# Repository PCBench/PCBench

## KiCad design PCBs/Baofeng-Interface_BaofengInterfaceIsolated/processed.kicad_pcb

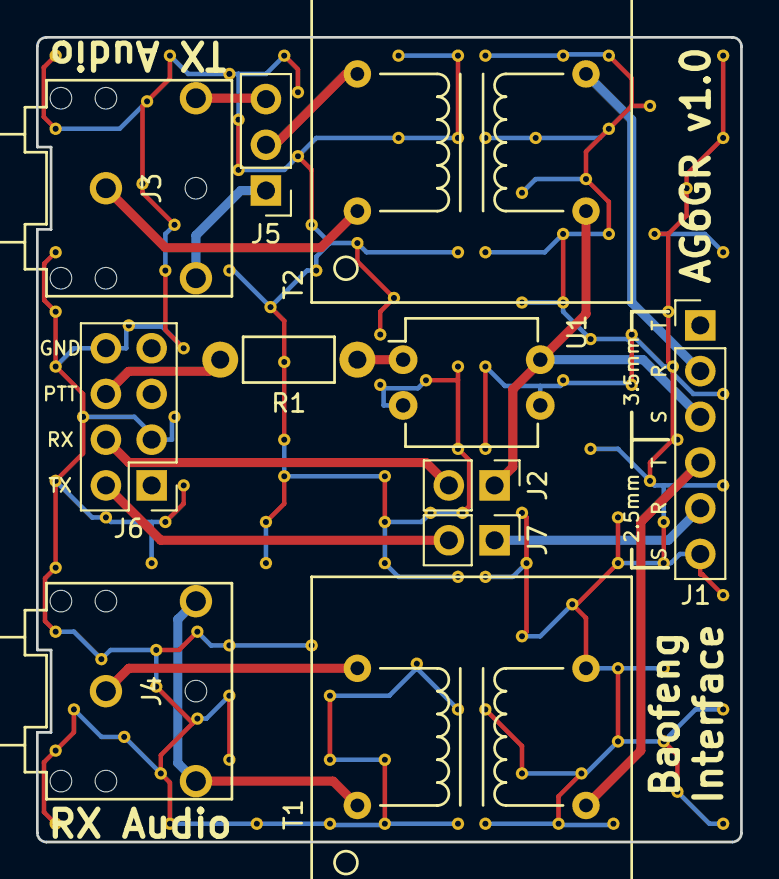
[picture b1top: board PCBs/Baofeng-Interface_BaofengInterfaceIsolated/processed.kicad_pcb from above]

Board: 2 copper layers, 39.1 x 44.7 mm, 11 parts (0 on the bottom side), 16 nets.

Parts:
J1: CONN_01X06; Pin_Header_Straight_1x06_Pitch2.54mm
J2, J7: CONN_01X02; Pin_Header_Straight_1x02_Pitch2.54mm
J3, J4: JACK_TRS_3PINS; SJ1-352XN
J5: CONN_01X03; Pin_Header_Straight_1x03_Pitch2.54mm
J6: CONN_02X04; Pin_Header_Straight_2x04_Pitch2.54mm
R1: 100; Resistor_Horizontal_RM7mm
T1, T2: LM-NP-1001-B1L; LM-LP-1001L
U1: LTV-817; DIP-4_W7.62mm

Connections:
GND: J6.3, J6.8, U1.2
GNDA: J1.6, T1.5, U1.3
unnamed: J1.5, J7.1
unnamed: J3.1, T2.1
unnamed: J4.1, T1.4
unnamed: J4.2, J4.3, T1.1
unnamed: J5.2, T2.4
unnamed: R1.1, U1.1
PTT_B: J6.6, R1.2
RX_AUDIO: J1.4, T1.8
SERIAL_RX: J2.2, J6.4
SERIAL_TX: J6.2, J7.2
TX_AUDIO+: J1.2, T2.5
TX_AUDIO-: J1.3, J2.1, T2.8, U1.4
TX_LEFT+: J3.3, J5.3
TX_RIGHT+: J3.2, J5.1

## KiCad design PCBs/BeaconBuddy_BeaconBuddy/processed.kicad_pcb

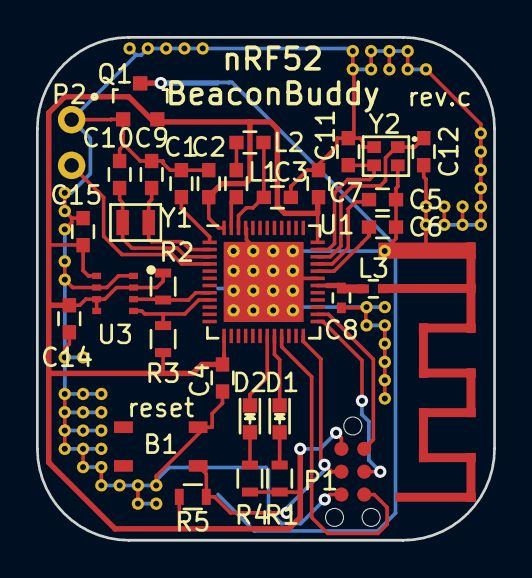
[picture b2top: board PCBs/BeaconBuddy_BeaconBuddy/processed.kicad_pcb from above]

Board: 2 copper layers, 25.4 x 27.9 mm, 34 parts (1 on the bottom side), 26 nets.

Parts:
A1: Antenna; Antenna-2.45GHZ
B1: SKRPABE010
BT1: BAT-HLD-001; BATT-HLD-001
C1, C4, C7, C14, C15: 0.1uF; C_0603
C2: 4.7uF; C_0603
C3: 1uF; C_0603
C5: 100pF; C_0603
C6: NC; C_0603
C8: 0.8pF; C_0402
C9, C10, C11, C12: 12pF; C_0603
D1: L0603G; LED_0603
D2: L0603R; LED_0603
L1: 10uH; C_0603
L2: 15nH; C_0603
L3: 3.9nH; C_0402
P1: CONN_01X06; TC2030-MCP-NL
P2: AIN0; CONN_100mil_1x2
Q1: Si2365EDS; SOT-23
R1, R4: 470; R_0603
R2, R3: 4.7k; R_0603
R5: 10k; R_0603
U1: nRF52832-QFAA; UQFN-48-1EP_6x6mm_Pitch0.4mm
U3: BME280; Bosch_LGA8_2.5x2.5
Y1: 32.768kHz; Crystal_ABS06
Y2: 32MHz; Crystal_ABM11

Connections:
/AIN0: P2.2, U1.4
/ANT: C8.1, L3.2, U1.30
/RF_OUT: A1.1, L3.1
/SCL: R3.2, U1.9, U3.4
/SDA: R2.2, U1.8, U3.3
/SWDCLK: P1.4, U1.25
/SWDIO: P1.2, U1.26
/SWO: P1.6, U1.21
/XC1: C11.2, U1.35, Y2.3
/XC2: C12.2, U1.34, Y2.1
/XL1: C9.2, U1.2, Y1.1
/XL2: C10.2, U1.3, Y1.2
/nRESET: B1.1, P1.3, R5.2, U1.24
GND: A1.2, B1.3, BT1.2, C1.2, C2.2, C3.2, C4.2, C5.1, C6.1, C7.2, C8.2, C9.1, C10.1, C11.1, C12.1, C14.2, C15.2, P1.5, P2.1, Q1.1, U1.31, U1.45, U1.49, U3.1, U3.7, Y2.2, Y2.4
unnamed: BT1.1, Q1.3
unnamed: C1.1, U1.1
unnamed: C3.1, L2.1, U1.46
unnamed: C5.2, U1.33
unnamed: C6.2, U1.32
unnamed: D1.1, U1.20
unnamed: D1.2, R1.1
unnamed: D2.1, U1.19
unnamed: D2.2, R4.1
unnamed: L1.1, L2.2
unnamed: L1.2, U1.47
VDD: C2.1, C4.1, C7.1, C14.1, C15.1, P1.1, Q1.2, R1.2, R2.1, R3.1, R4.2, R5.1, U1.13, U1.36, U1.48, U3.2, U3.5, U3.6, U3.8

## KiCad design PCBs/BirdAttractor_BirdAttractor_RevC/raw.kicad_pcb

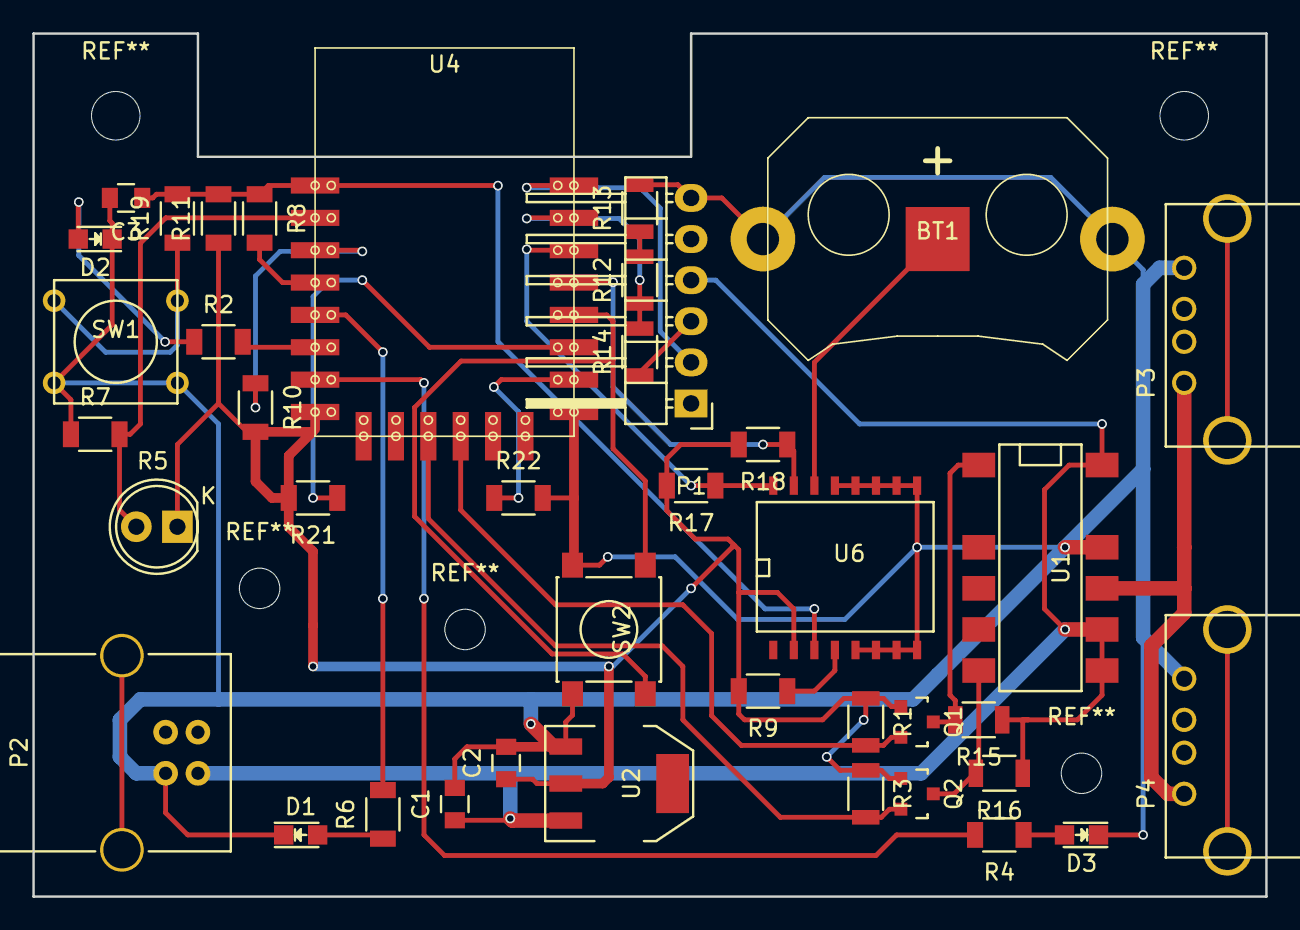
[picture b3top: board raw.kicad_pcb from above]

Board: 2 copper layers, 76.2 x 53.3 mm, 40 parts (0 on the bottom side), 30 nets.

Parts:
BT1: 3V Battery; BK-913
C1, C2: 10uF; C_0805
C3: 0.1uF; C_0805
D1, D2, D3: LED; LED-0805
P1: FTDI; Pin_Header_Angled_1x06
P2: USB_B
P3, P4: USB_A
Q1, Q2: BSS138; SOT-23
R1, R3, R12, R13, R15, R16: 10K; R_1206
R2, R4: 68; C_1206
R5: Photores; LED-5MM
R6: 18; C_1206
R7, R19: 1K; C_1206
R8: 2.7K; C_1206
R9, R10, R11, R21, R22: 10K; C_1206
R14: 10K/0; R_1206
R17, R18: 47K; C_1206
SW1: SW_PUSH; SW_PUSH_SMALL
SW2: SW_PUSH; SW_SPST_PTS645
U1: PR_Relay_V23079; DIP-12-SMD
U2: AMS1117-3.3; SOT-223
U4: ESP8266-12E; ESP8266-12E-80
U6: DS3231; SO-16-W

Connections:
5V_IN: C1.1, P1.4, P2.1, R15.1, R16.1, U1.7, U1.8, U1.12, U2.3
5V_OUT: P3.1, P4.1, U1.9
ADC: R5.2, R7.2, U4.2
ALARM_WAKE: C3.1, R8.1, R11.2, R19.2, U4.1, U6.3
CH_PD: R10.1, U4.3
DEEP_SLEEP_WAKE: R8.2, U4.4
GND: BT1.2, C1.2, C2.2, C3.2, D1.1, D2.1, D3.1, P1.6, P2.4, P3.4, P4.4, R7.1, R13.2, R22.2, SW1.2, SW2.2, U1.10, U2.1, U4.15, U6.5, U6.6, U6.7, U6.8, U6.9, U6.10, U6.11, U6.12, U6.13
LED_5V_IN: R2.2, U4.6
LED_5V_OUT: R4.2, U4.7
LED_WIFI: R6.2, U4.5
unnamed: D1.2, R6.1
unnamed: D2.2, R2.1
unnamed: D3.2, R4.1
unnamed: R9.1, U6.4
unnamed: R12.2, R13.1
unnamed: R19.1, SW1.1
unnamed: R21.1, U4.17
unnamed: R22.1, U4.16
PROGRAM: SW2.1, U4.18
RELAY_OFF: Q1.3, R15.2, U1.1
RELAY_OFF33: Q1.2, R1.2, U4.12
RELAY_ON: Q2.3, R16.2, U1.6
RELAY_ON33: Q2.2, R3.2, U4.11
RX: P1.3, R14.1
RX33: R12.1, R14.2, U4.21
SCL: R17.1, U4.20, U6.16
SDA: R18.1, U4.19, U6.15
TX: P1.2, U4.22
V33: C2.1, Q1.1, Q2.1, R1.1, R3.1, R5.1, R9.2, R10.2, R11.1, R17.2, R18.2, R21.2, U2.2, U4.8, U6.2
VBAT: BT1.1, U6.14

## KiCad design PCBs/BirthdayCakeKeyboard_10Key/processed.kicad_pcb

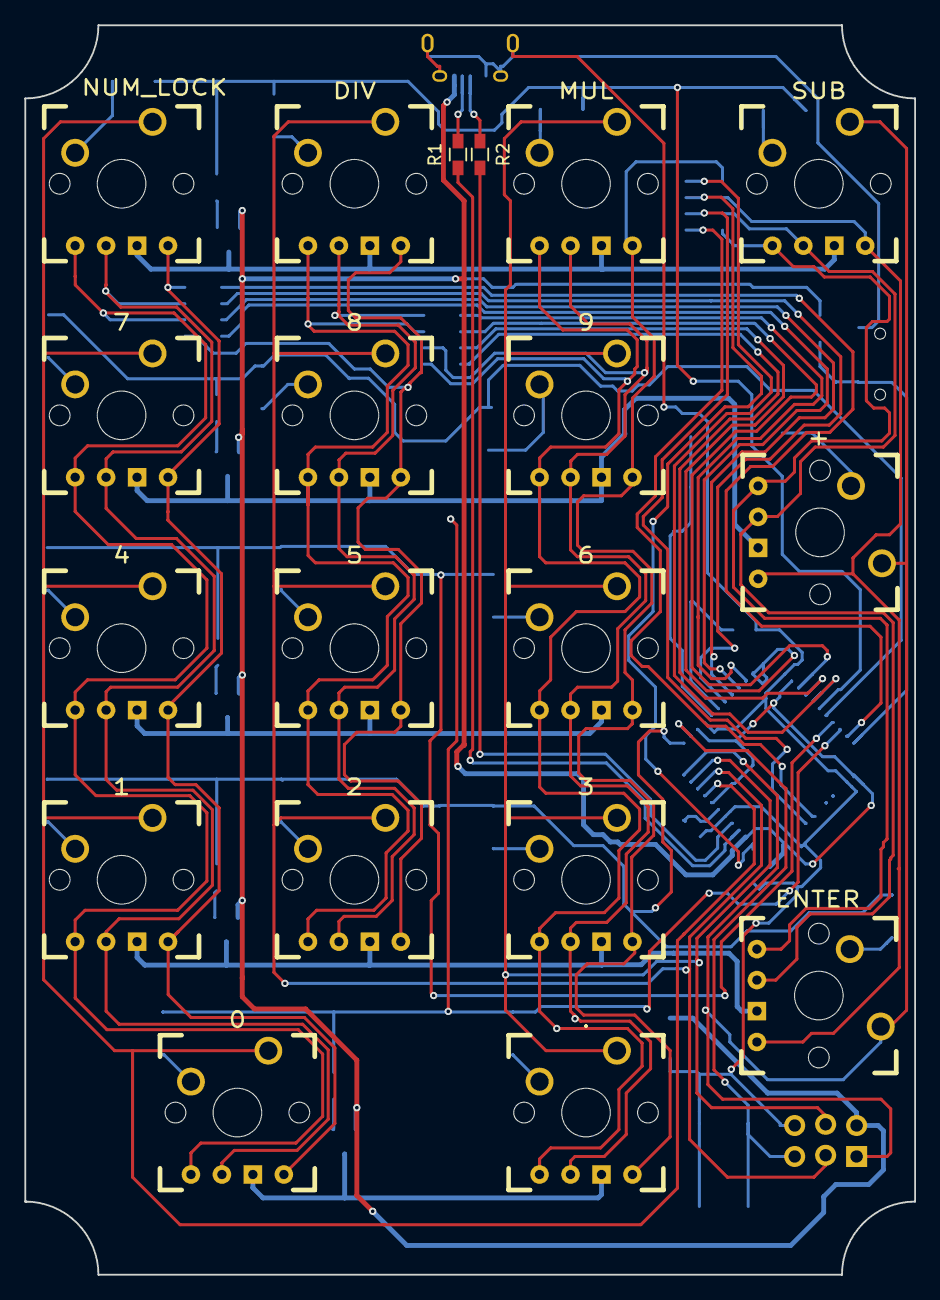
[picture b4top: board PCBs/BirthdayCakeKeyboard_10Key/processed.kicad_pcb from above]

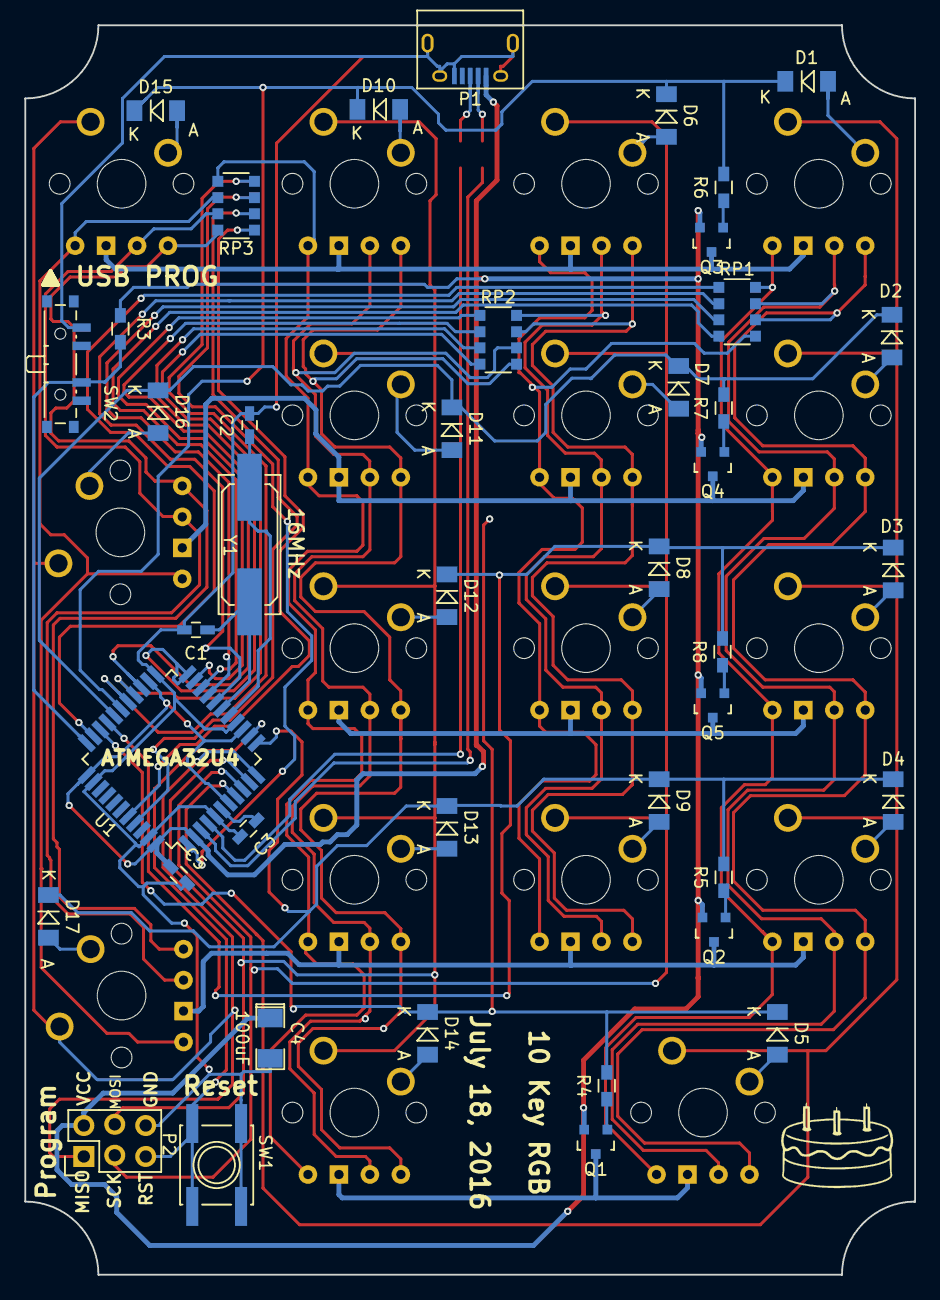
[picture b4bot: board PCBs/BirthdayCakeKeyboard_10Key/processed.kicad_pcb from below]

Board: 2 copper layers, 73.0 x 102.5 mm, 65 parts (46 on the bottom side), 71 nets.

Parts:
C1, C2: 18pF; C_0603_HandSoldering
C3: .1uF; C_0603_HandSoldering
C4: 100uF; SMD-1206_Pol
C5: 0.1uF; C_0603_HandSoldering
D1, D2, D3, D4, D5, D6, D7, D8, D9, D10, D11, D12, D13, D14, D15, D16, D17: D; MiniMELF_Standard
Noname_1: BirthdayCake
Noname_2, Noname_3, Noname_4: Flame
P1: USB_OTG; USB_Micro-B
P2: Program; Pin_Header_Straight_2x03
Q1, Q2, Q3, Q4, Q5: MMBT3906; SOT-23
R1, R2: 22; R_0603_HandSoldering
R3: 10k; R_0603_HandSoldering
R4, R5, R6, R7, R8: 1K; R_0603_HandSoldering
RP1, RP2, RP3: 100; R_Array_Convex_4x1206
SW1: SW_PUSH; SW_SPST_EVQQ2
SW2: USB PROG; SW_SP3T_PCM13
SW3: NUM_LOCK; Zealios_Cherry_MX
SW4: 7; Zealios_Cherry_MX
SW5: 4; Zealios_Cherry_MX
SW6: 1; Zealios_Cherry_MX
SW7: 0; Zealios_Cherry_MX
SW8: DIV; Zealios_Cherry_MX
SW9: 8; Zealios_Cherry_MX
SW10: 5; Zealios_Cherry_MX
SW11: 2; Zealios_Cherry_MX
SW12: MUL; Zealios_Cherry_MX
SW13: 9; Zealios_Cherry_MX
SW14: 6; Zealios_Cherry_MX
SW15: 3; Zealios_Cherry_MX
SW16: .; Zealios_Cherry_MX
SW17: SUB; Zealios_Cherry_MX
SW18: +; Zealios_Cherry_MX
SW19: ENTER; Zealios_Cherry_MX
U1: ATMEGA32U4-A; LQFP-44_10x10mm_Pitch0.8mm
Y1: 16Mhz; Q_49U3HMS

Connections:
/COL0: SW3.1, SW4.1, SW5.1, SW6.1, SW7.1, U1.8
/COL1: P2.3, SW8.1, SW9.1, SW10.1, SW11.1, U1.9
/COL2: P2.4, SW12.1, SW13.1, SW14.1, SW15.1, SW16.1, U1.10
/COL3: P2.1, SW17.1, SW18.1, SW19.1, U1.11
/LEDB0: RP1.6, SW3.6, SW4.6, SW5.6, SW6.6, SW7.6
/LEDB1: RP2.7, SW8.6, SW9.6, SW10.6, SW11.6
/LEDB2: RP2.5, SW12.6, SW13.6, SW14.6, SW15.6, SW16.6
/LEDB3: RP3.8, SW17.6, SW18.6, SW19.6
/LEDG0: RP1.7, SW3.5, SW4.5, SW5.5, SW6.5, SW7.5
/LEDG1: RP2.8, SW8.5, SW9.5, SW10.5, SW11.5
/LEDG2: RP2.6, SW12.5, SW13.5, SW14.5, SW15.5, SW16.5
/LEDG3: RP3.7, SW17.5, SW18.5, SW19.5
/LEDR0: RP1.8, SW3.3, SW4.3, SW5.3, SW6.3, SW7.3
/LEDR1: RP1.5, SW8.3, SW9.3, SW10.3, SW11.3
/LEDR2: RP3.5, SW12.3, SW13.3, SW14.3, SW15.3, SW16.3
/LEDR3: RP3.6, SW17.3, SW18.3, SW19.3
/PROGRAM: R3.2, SW2.2, U1.33
/ROW0: D1.1, D6.1, D10.1, D15.1, R6.2, U1.28
/ROW1: D2.1, D7.1, D11.1, D16.1, R7.2, U1.29
/ROW2: D3.1, D8.1, D12.1, R8.2, U1.30
/ROW3: D4.1, D9.1, D13.1, D17.1, R5.2, U1.12
/ROW4: D5.1, D14.1, R4.2, U1.31
/RST: P2.5, SW1.2, U1.13
/USBDMinus: R1.1, U1.3
/USBDPlus: R2.1, U1.4
GND: C1.2, C2.2, C3.2, C4.2, C5.2, P1.5, P1.6, P2.6, SW1.1, SW2.1, U1.5, U1.15, U1.23, U1.35, U1.43
unnamed: C1.1, U1.17, Y1.1
unnamed: C2.1, U1.16, Y1.2
unnamed: C3.1, U1.6
unnamed: D1.2, SW3.2
unnamed: D2.2, SW4.2
unnamed: D3.2, SW5.2
unnamed: D4.2, SW6.2
unnamed: D5.2, SW7.2
unnamed: D6.2, SW8.2
unnamed: D7.2, SW9.2
unnamed: D8.2, SW10.2
unnamed: D9.2, SW11.2
unnamed: D10.2, SW12.2
unnamed: D11.2, SW13.2
unnamed: D12.2, SW14.2
unnamed: D13.2, SW15.2
unnamed: D14.2, SW16.2
unnamed: D15.2, SW17.2
unnamed: D16.2, SW18.2
unnamed: D17.2, SW19.2
unnamed: P1.2, R1.2
unnamed: P1.3, R2.2
unnamed: Q1.1, R4.1
unnamed: Q1.3, SW7.4, SW16.4
unnamed: Q2.1, R5.1
unnamed: Q2.3, SW6.4, SW11.4, SW15.4, SW19.4
unnamed: Q3.1, R6.1
unnamed: Q3.3, SW3.4, SW8.4, SW12.4, SW17.4
unnamed: Q4.1, R7.1
unnamed: Q4.3, SW4.4, SW9.4, SW13.4, SW18.4
unnamed: Q5.1, R8.1
unnamed: Q5.3, SW5.4, SW10.4, SW14.4
unnamed: RP1.1, U1.32
unnamed: RP1.2, U1.18
unnamed: RP1.3, U1.19
unnamed: RP1.4, U1.20
unnamed: RP2.1, U1.21
unnamed: RP2.2, U1.25
unnamed: RP2.3, U1.22
unnamed: RP2.4, U1.26
unnamed: RP3.1, U1.40
unnamed: RP3.2, U1.41
unnamed: RP3.3, U1.1
unnamed: RP3.4, U1.27
VCC: C4.1, C5.1, P1.1, P2.2, Q1.2, Q2.2, Q3.2, Q4.2, Q5.2, R3.1, U1.2, U1.7, U1.14, U1.24, U1.34, U1.44

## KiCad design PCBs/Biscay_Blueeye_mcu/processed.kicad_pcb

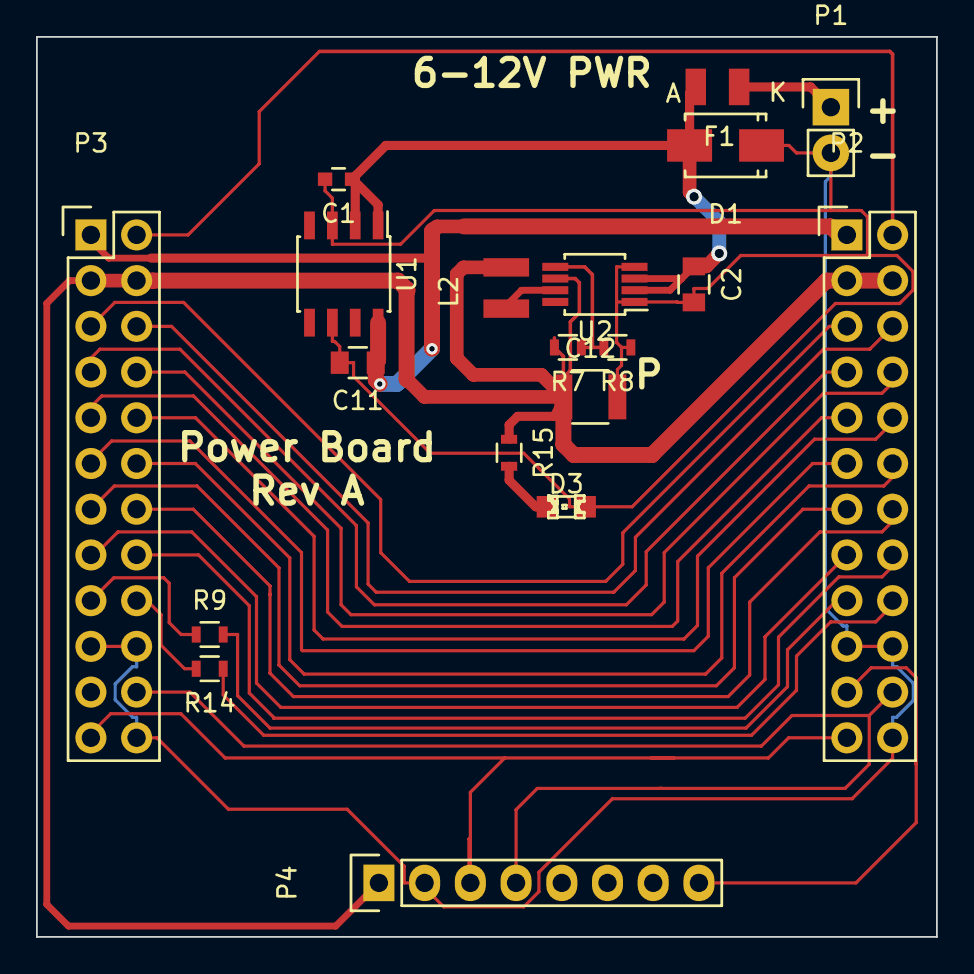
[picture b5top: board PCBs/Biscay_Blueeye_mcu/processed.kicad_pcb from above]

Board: 2 copper layers, 50.0 x 50.0 mm, 19 parts (0 on the bottom side), 28 nets.

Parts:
C1: 1u; C_0603
C2: 10u; C_0805
C11: 4.7u; C_0805
C12: 22u; C_1210
D1: >2A; Diode-SMA_Standard
D3: GREEN; LED-0805
F1: 2A poly; Fuse_SMD1206_Reflow
L2: VLF252015MT-2R2M; Neosid_Inductor_SM-NE29_SMD1008
P1: 6V PWR; Pin_Header_Straight_1x02
P2, P3: FPGA; Pin_Header_Straight_2x12
P4: MPU9150; Pin_Header_Straight_1x08
R7: 715k; R_0603
R8: 180k; R_0603
R9, R14: 10k; R_0603
R15: 330; R_0603
U1: LK115D50; SOIC-8_3.9x4.9mm_Pitch1.27mm
U2: TPS62160; MSOP-8_3x3mm_Pitch0.65mm

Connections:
+3V3: C12.1, L2.2, P2.3, P2.4, P3.3, P3.4, P4.1, R7.2, R15.1, U2.6
+5V: C11.1, P2.1, P3.1, U1.8
+BATT: C1.1, C2.1, D1.2, F1.2, U1.1, U1.2, U2.2, U2.3
/ACC_INT: P2.21, P4.8
/CAPTD: P2.10, P3.10
/CLR: P2.11, P3.11
/DAC_MOSI: P2.13, P3.13
/DAC_SCLK: P2.14, P3.14
/DAC_~SYNC: P2.15, P3.15
/FPGA_MISO: P2.8, P3.8
/FPGA_MOSI: P2.7, P3.7
/FPGA_SCK: P2.5, P3.5
/FPGA_SCL: P2.23, P3.23, P4.3
/FPGA_SDA: P2.22, P3.22, P4.4
/FPGA_~CS0: P2.6, P3.6
/FPGA_~CS1: P2.12, P3.12
/MON_5VA: P2.2, P3.2
/REG_EN: P2.16, P3.16
/TEMPS: P2.18, R14.1
/TRIGD: P2.9, P3.9
/Vb_MON: P2.17, R9.2
GND: C1.2, C2.2, C11.2, C12.2, D1.1, D3.2, P1.2, P2.19, P2.20, P2.24, P3.19, P3.20, P3.24, P4.2, R8.1, U1.3, U1.6, U2.1, U2.4
unnamed: D3.1, R15.2
unnamed: F1.1, P1.1
unnamed: L2.1, U2.7
unnamed: P3.17, R9.1
unnamed: P3.18, R14.2
unnamed: R7.1, R8.2, U2.5

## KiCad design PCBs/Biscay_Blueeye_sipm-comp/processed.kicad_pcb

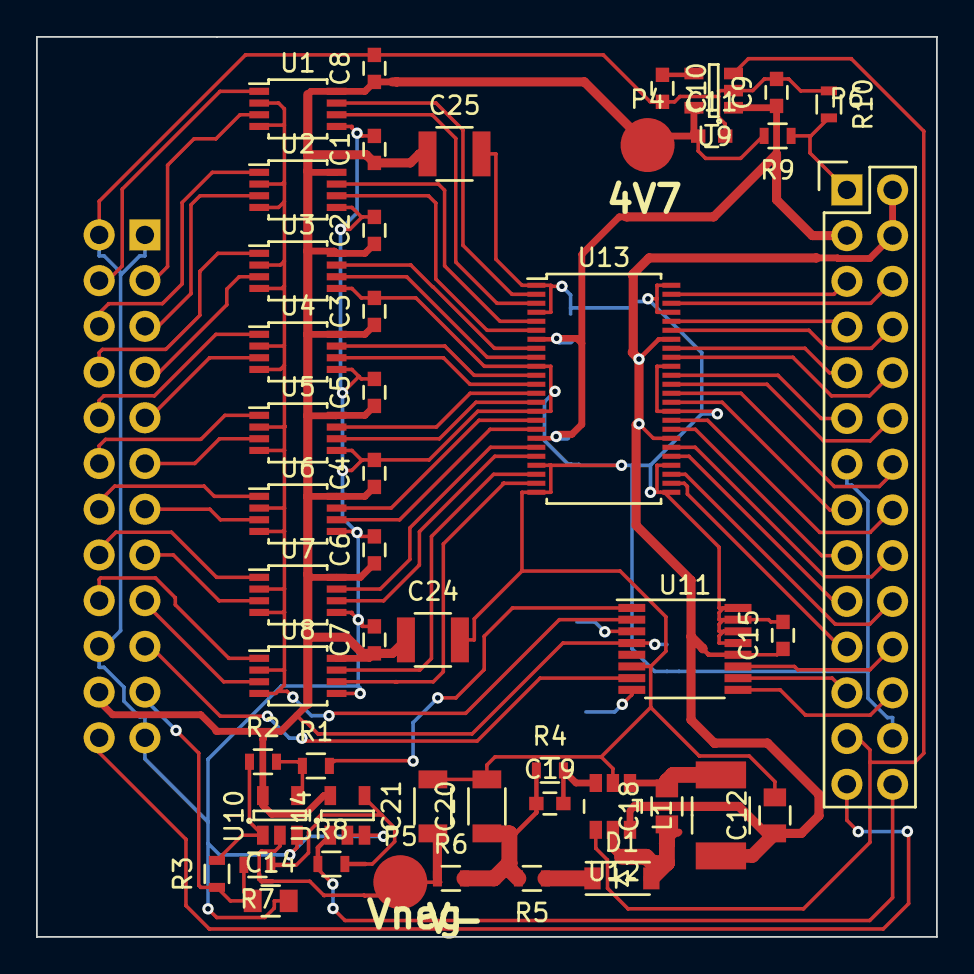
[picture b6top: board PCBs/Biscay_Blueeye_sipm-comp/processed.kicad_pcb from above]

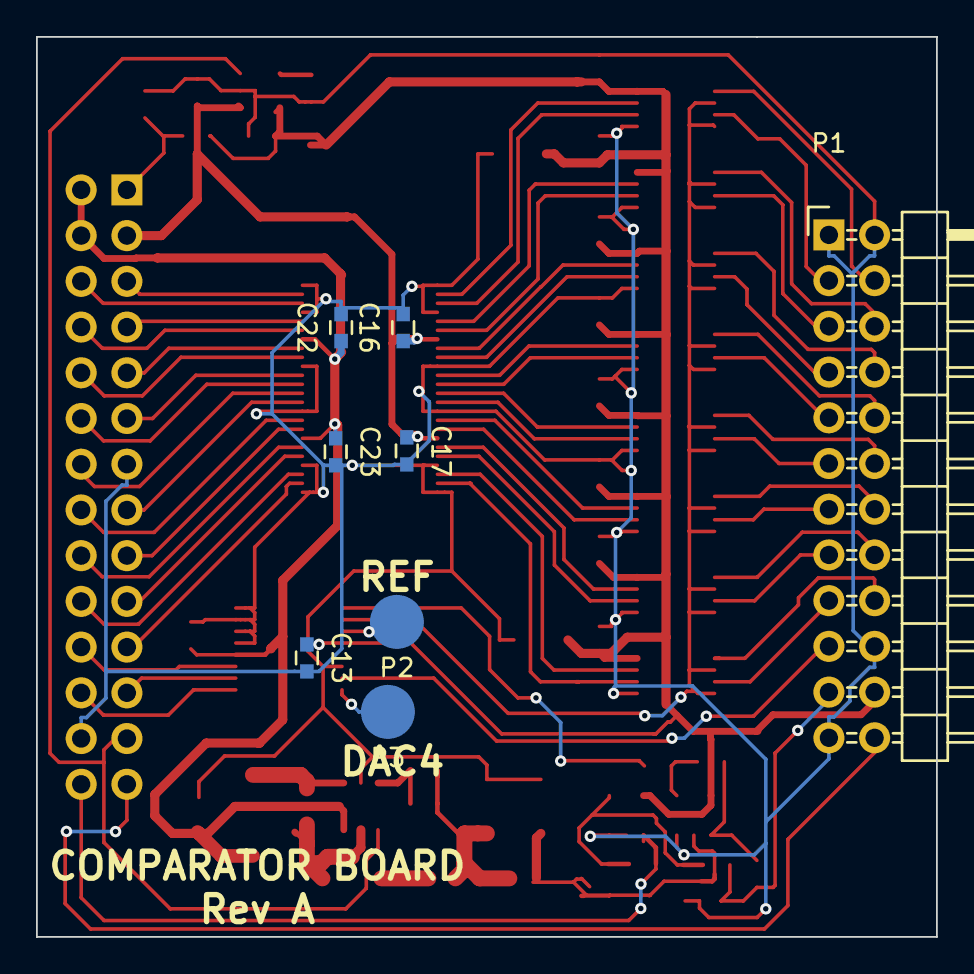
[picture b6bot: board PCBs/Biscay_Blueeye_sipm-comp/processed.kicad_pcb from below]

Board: 2 copper layers, 50.0 x 50.0 mm, 57 parts (8 on the bottom side), 75 nets.

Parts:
C1, C2, C3, C4, C5, C6, C7, C8, C9, C11, C13, C15, C16, C17, C22, C23: 1u; C_0603
C10: 10n; C_0603
C12: 4.7u; C_0805
C14, C18: 0.1u; C_0805
C19: 5p; C_0603
C20, C21: 1u; C_1206
C24, C25: 22u; C_1210
D1: MBR0540; SOD-123
L1: 10u; Neosid_Inductor_SM-NE45_SMD1812
P1: CONN_02X12; Pin_Header_Angled_2x12
P2: REFO; Measurement_Point_Round-SMD-Pad_Big
P3: AUXDAC; Measurement_Point_Round-SMD-Pad_Big
P4: 5VA; Measurement_Point_Round-SMD-Pad_Big
P5: Vneg; Measurement_Point_Round-SMD-Pad_Big
P6: CONN_01X28; Pin_Header_Straight_2x14
R1, R3: 1k; R_0603
R2, R8: 15k; R_0603
R4: 3.4M; R_0603
R5: 39; R_0603
R6: 100; R_0603
R7: 100k; R_0603
R9, R10: 10k; R_0603
U1, U2, U3, U4, U5, U6, U7, U8: MAX9012; TSSOP-8_3x3mm_Pitch0.65mm
U9: LD3985M47R; SOT-23-5
U10: LT6015; SOT-23-5
U11: DAC7564; TSSOP-16_4.4x5mm_Pitch0.65mm
U12: LT3483; TSOT-6-MK06A
U13: SN74LVCH16T245; TSSOP-48_6.1x12.5mm_Pitch0.5mm
U14: LT6003; SOT-23-5

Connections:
+3V3: C12.1, C15.1, C22.1, C23.1, L1.1, P6.2, P6.4, U11.12, U12.6, U13.31, U13.42
+5V: C9.1, C16.1, C17.1, P6.3, U9.1, U13.7, U13.18
+5VA: C1.1, C2.1, C3.1, C4.1, C5.1, C6.1, C7.1, C8.1, C11.1, C13.1, C24.1, C25.1, P1.22, P4.1, R9.2, U1.8, U2.8, U3.8, U4.8, U5.8, U6.8, U7.8, U8.8, U9.5, U10.5, U11.4, U14.5
/AMP_1: P1.11, U5.3
/AMP_2: P1.15, U7.3
/AMP_3: P1.8, U3.1
/AMP_4: P1.9, U4.3
/AMP_5: P1.13, U6.3
/AMP_6: P1.16, U7.1
/AMP_7: P1.7, U3.3
/AMP_8: P1.10, U4.1
/AMP_9: P1.18, U8.1
/AMP_10: P1.17, U8.3
/AMP_11: P1.5, U2.3
/AMP_12: P1.6, U2.1
/AMP_13: P1.14, U6.1
/AMP_14: P1.12, U5.1
/AMP_15: P1.3, U1.3
/AMP_16: P1.4, U1.1
/COMP_1: U5.6, U13.14
/COMP_2: U7.6, U13.20
/COMP_3: U3.7, U13.8
/COMP_4: U4.6, U13.12
/COMP_5: U6.6, U13.17
/COMP_6: U7.7, U13.19
/COMP_7: U3.6, U13.9
/COMP_8: U4.7, U13.11
/COMP_9: U8.7, U13.22
/COMP_10: U8.6, U13.23
/COMP_11: U2.6, U13.6
/COMP_12: U2.7, U13.5
/COMP_13: U6.7, U13.16
/COMP_14: U5.7, U13.13
/COMP_15: U1.6, U13.3
/COMP_16: U1.7, U13.2
/DAC_Din: P6.22, U11.11
/DAC_SCLK: P6.23, U11.10
/DAC_~SYNC: P6.24, U11.9
/MON_5VA: P6.1, R9.1, R10.2
/OUT_1: P6.15, U13.35
/OUT_2: P6.19, U13.29
/OUT_3: P6.9, U13.41
/OUT_4: P6.12, U13.37
/OUT_5: P6.17, U13.32
/OUT_6: P6.18, U13.30
/OUT_7: P6.10, U13.40
/OUT_8: P6.11, U13.38
/OUT_9: P6.20, U13.27
/OUT_10: P6.21, U13.26
/OUT_11: P6.8, U13.43
/OUT_12: P6.7, U13.44
/OUT_13: P6.16, U13.33
/OUT_14: P6.14, U13.36
/OUT_15: P6.6, U13.46
/OUT_16: P6.5, U13.47
/TEMPS: P1.24, P6.27
/Vb_MON: P6.28, R8.1, U14.1
GND: C1.2, C2.2, C3.2, C4.2, C5.2, C6.2, C7.2, C8.2, C9.2, C10.2, C11.2, C12.2, C13.2, C14.2, C15.2, C16.2, C17.2, C20.2, C21.2, C22.2, C23.2, C24.2, C25.2, P1.1, P1.2, P1.20, P1.23, P6.13, P6.26, R10.1, U1.5, U2.5, U3.5, U4.5, U5.5, U6.5, U7.5, U8.5, U9.2, U10.3, U11.6, U11.13, U11.14, U11.15, U11.16, U12.2, U13.1, U13.4, U13.10, U13.15, U13.21, U13.24, U13.25, U13.28, U13.34, U13.39, U13.45, U13.48, U14.2, U14.3
unnamed: C10.1, U9.4
unnamed: C18.1, D1.2, U12.5
unnamed: C18.2, L1.2, U12.1
unnamed: C19.1, C20.1, R4.1, R5.2, R6.2
unnamed: C19.2, R4.2, U12.3
unnamed: D1.1, R5.1
unnamed: P2.1, U11.3
unnamed: P3.1, U11.8
unnamed: R1.1, R2.2, U10.4
unnamed: R2.1, R3.2, U10.1
unnamed: R7.1, R8.2, U14.4
REG_EN: P6.25, U9.3, U12.4
Vbias: C14.1, P1.21, R3.1, R7.2
Vbias_SET: R1.2, U11.1
Vmid: P1.19, U11.7
Vneg: C21.1, P5.1, R6.1, U10.2
Vset: U1.2, U1.4, U2.2, U2.4, U3.2, U3.4, U4.2, U4.4, U5.2, U5.4, U6.2, U6.4, U7.2, U7.4, U8.2, U8.4, U11.2

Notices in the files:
PCBs/BirdAttractor_BirdAttractor_RevC/raw.kicad_pcb:
MIT License
